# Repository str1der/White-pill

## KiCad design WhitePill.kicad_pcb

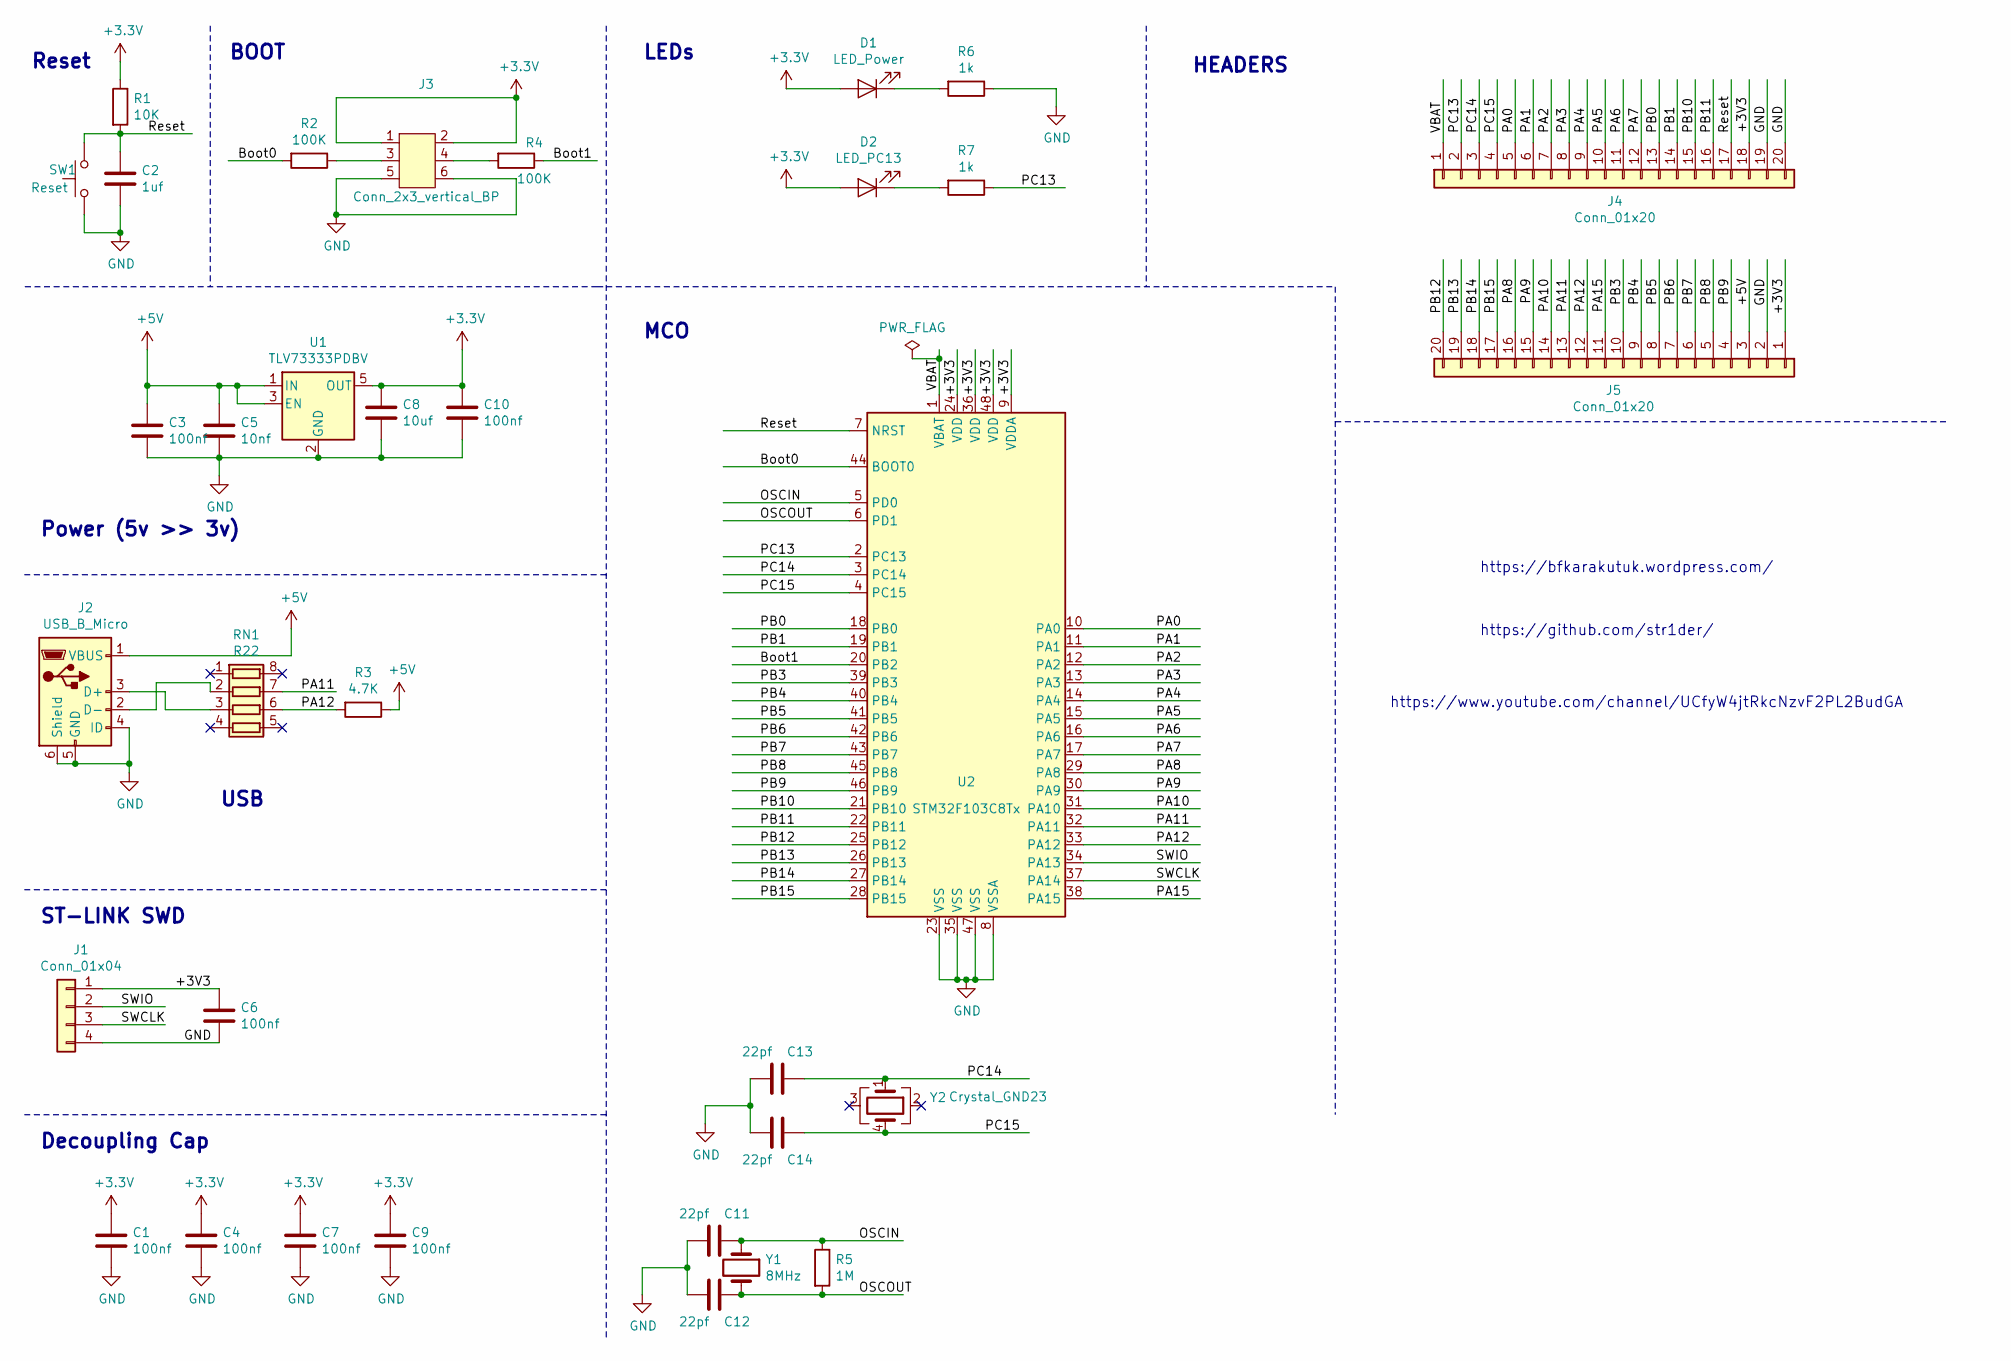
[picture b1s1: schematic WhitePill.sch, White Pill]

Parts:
C1, C3, C4, C6, C7, C9, C10: 100nf; C_0805_2012Metric
C2: 1uf; C_0805_2012Metric
C5: 10nf; C_0805_2012Metric
C8: 10uf; C_0805_2012Metric
C11, C12, C13, C14: 22pf; C_0805_2012Metric
D1: LED_Power; LED_0805_2012Metric
D2: LED_PC13; LED_0805_2012Metric
J1: Conn_01x04; PinHeader_1x04_P2.54mm_Horizontal
J2: USB_B_Micro; USB_Micro-B_Unknown_5s_SMT
J3: Conn_2x3_vertical_BP; PinHeader_2x03_P2.54mm_Vertical
J4, J5: Conn_01x20; PinHeader_1x20_P2.54mm_Vertical
R1: 10K; R_0805_2012Metric
R2, R4: 100K; R_0805_2012Metric
R3: 4.7K; R_0603_1608Metric
R5: 1M; R_0805_2012Metric
R6, R7: 1k; R_0805_2012Metric
RN1: R22; R_Array_Concave_4x0603
SW1: Reset; SW_SPST_CK_RS282G05A3
U1: TLV73333PDBV; SOT-23-5
U2: STM32F103C8Tx; LQFP-48_7x7mm_P0.5mm
Y1: 8MHz; Crystal_HC49-4H_Vertical
Y2: Crystal_GND23; RSM200S

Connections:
+5V: C3.1, C5.1, J2.1 (VBUS), J5.3, R3.1, U1.1 (IN), U1.3 (EN)
/Boot0: R2.2, U2.44 (BOOT0)
/Boot1: R4.1, U2.20 (PB2)
/OSCIN: C11.1, R5.1, U2.5 (PD0), Y1.1
/OSCOUT: C12.1, R5.2, U2.6 (PD1), Y1.2
/PA0: J4.5, U2.10 (PA0)
/PA1: J4.6, U2.11 (PA1)
/PA2: J4.7, U2.12 (PA2)
/PA3: J4.8, U2.13 (PA3)
/PA4: J4.9, U2.14 (PA4)
/PA5: J4.10, U2.15 (PA5)
/PA6: J4.11, U2.16 (PA6)
/PA7: J4.12, U2.17 (PA7)
/PA8: J5.16, U2.29 (PA8)
/PA9: J5.15, U2.30 (PA9)
/PA10: J5.14, U2.31 (PA10)
/PA11: J5.13, RN1.7 (R2.2), U2.32 (PA11)
/PA12: J5.12, R3.2, RN1.6 (R3.2), U2.33 (PA12)
/PA15: J5.11, U2.38 (PA15)
/PB0: J4.13, U2.18 (PB0)
/PB1: J4.14, U2.19 (PB1)
/PB3: J5.10, U2.39 (PB3)
/PB4: J5.9, U2.40 (PB4)
/PB5: J5.8, U2.41 (PB5)
/PB6: J5.7, U2.42 (PB6)
/PB7: J5.6, U2.43 (PB7)
/PB8: J5.5, U2.45 (PB8)
/PB9: J5.4, U2.46 (PB9)
/PB10: J4.15, U2.21 (PB10)
/PB11: J4.16, U2.22 (PB11)
/PB12: J5.20, U2.25 (PB12)
/PB13: J5.19, U2.26 (PB13)
/PB14: J5.18, U2.27 (PB14)
/PB15: J5.17, U2.28 (PB15)
/PC13: J4.2, R7.1, U2.2 (PC13)
/PC14: C13.1, J4.3, U2.3 (PC14), Y2.1
/PC15: C14.1, J4.4, U2.4 (PC15), Y2.4
/Reset: C2.1, J4.17, R1.2, SW1.2, U2.7 (NRST)
/SWCLK: J1.3, U2.37 (PA14)
/SWIO: J1.2, U2.34 (PA13)
/VBAT: J4.1, U2.1 (VBAT)
GND: C1.2, C2.2, C3.2, C4.2, C5.2, C6.2, C7.2, C8.2, C9.2, C10.2, C11.2, C12.2, C13.2, C14.2, J1.4, J2.4 (ID), J2.5 (GND), J2.6 (Shield), J3.5, J3.6, J4.19, J4.20, J5.2, R6.1, SW1.1, U1.2 (GND), U2.8 (VSSA), U2.23 (VSS), U2.35 (VSS), U2.47 (VSS)
unnamed: D1.1 (K), R6.2
unnamed: D2.1 (K), R7.2
unnamed: J2.2 (D-), RN1.2 (R2.1)
unnamed: J2.3 (D+), RN1.3 (R3.1)
unnamed: J3.3, R2.1
unnamed: J3.4, R4.2

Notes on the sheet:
Reset
BOOT
LEDs
HEADERS
Power (5v >> 3v)
USB
ST-LINK SWD
Decoupling Cap
MCO
https://bfkarakutuk.wordpress.com/
https://github.com/str1der/
https://www.youtube.com/channel/UCfyW4jtRkcNzvF2PL2BudGA

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
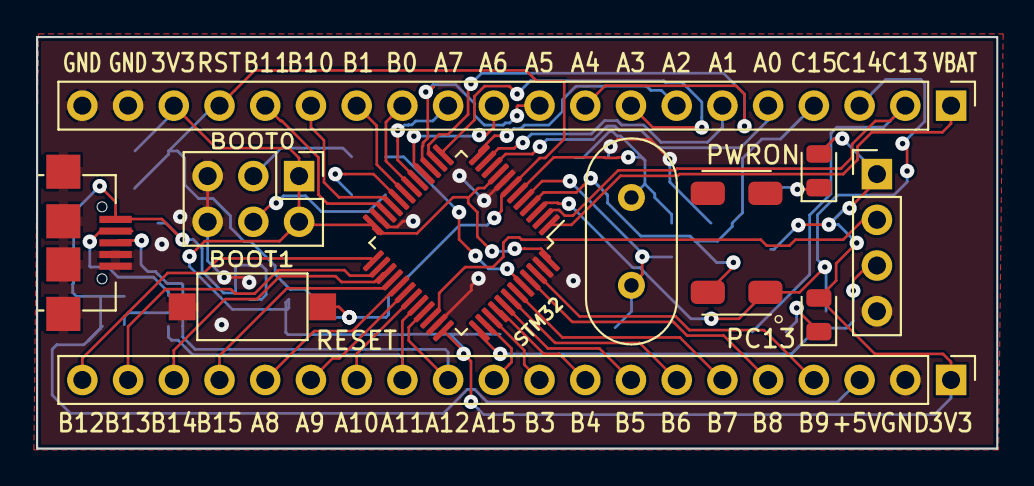
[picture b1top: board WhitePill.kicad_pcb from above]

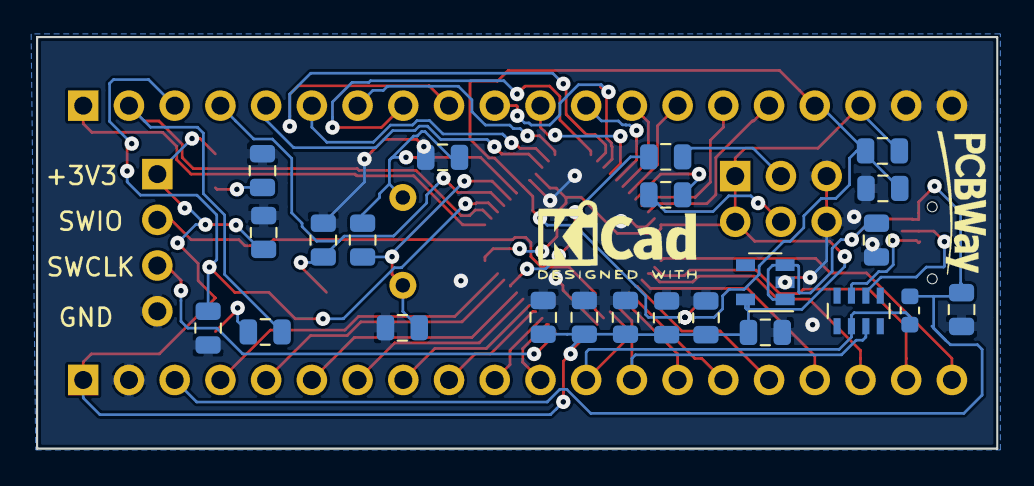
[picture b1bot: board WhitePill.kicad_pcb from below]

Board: 2 copper layers, 53.3 x 22.9 mm, 34 parts (23 on the bottom side), 49 nets.

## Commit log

2021-01-18 Add Pictures
